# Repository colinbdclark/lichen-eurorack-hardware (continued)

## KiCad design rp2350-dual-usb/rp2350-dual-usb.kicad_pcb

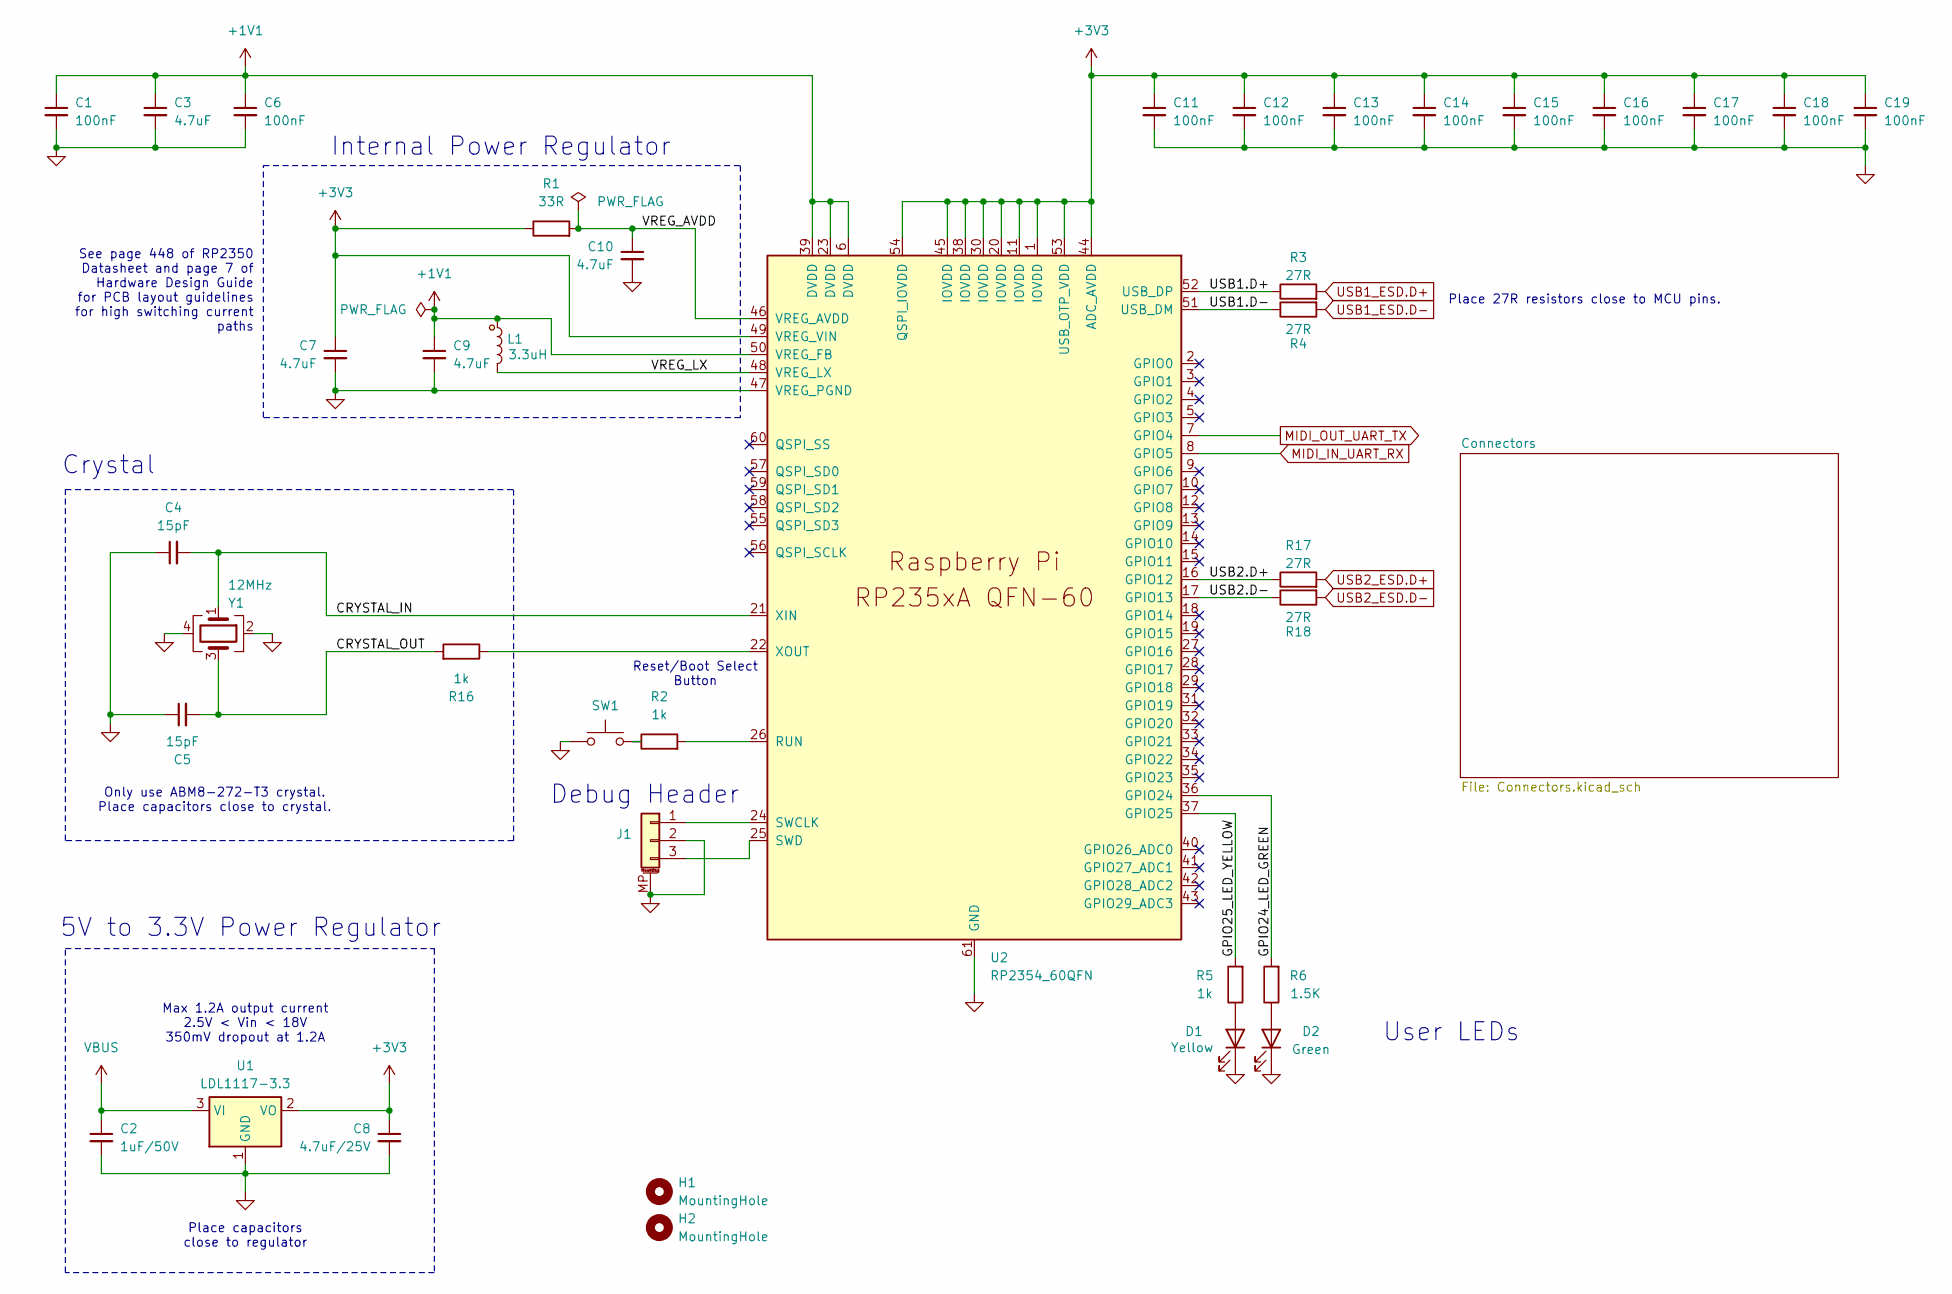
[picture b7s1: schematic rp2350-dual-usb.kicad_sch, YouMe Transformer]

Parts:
C1, C6, C11, C12, C13, C14, C15, C16, C17, C18, C19: 100nF; C_0402_1005Metric_small_pads; Part Number CL05B104KB54PNC; LCSC C307331
C2: 1uF; C_0805; Part Number CL21B105KBFNNNE; LCSC C28323
C3, C7, C9, C10: 4.7uF; C_0402_1005Metric_small_pads; Part Number CL05A475MP5NRNC; LCSC C23733
C4, C5: 15pF; C_0402_1005Metric_small_pads; Part Number 0402CG150J500NT; LCSC C1548
C8: 4.7uF; C_0805; Part Number CL21A475KAQNNNE; LCSC C1779
D1: Yellow; LED_0805_2012Metric_Pad1.15x1.40mm_HandSolder; Part Number KT-0805Y; LCSC C2296
D2: Green; LED_0805_2012Metric_Pad1.15x1.40mm_HandSolder; Part Number KT-0805G; LCSC C2297
H1, H2: MountingHole; MountingHole_2.2mm_M2
J1: Conn_01x03_MountingPin; JST_SH_SM03B-SRSS-TB_1x03-1MP_P1.00mm_Horizontal; Part Number SM03B-SRSS-TB; LCSC C160403
L1: 3.3uH; L_pol_2016; Part Number AOTA-B201610S3R3-101-T; LCSC C42411119
R1: 33R; R_0402_1005Metric; Part Number 0402WGF330JTCE; LCSC C25105
R2: 1k; R_0402_1005Metric; Part Number 0402WGF1001TCE; LCSC C11702
R3, R4, R17, R18: 27R; R_0402_1005Metric; Part Number 0402WGF270JTCE; LCSC C25100
R5, R16: 1K; R_0402_1005Metric; Part Number 0402WGF1001TCE; LCSC C11702
R6: 1.5K; R_0402_1005Metric; Part Number 0402WGF1501TCE; LCSC C25867
SW1: 1P1T Switch; SW_SPST_TS-1088-xR020; Part Number TS-1088-AR02016; LCSC C720477
U1: LDL1117-3.3; SOT-223-3_TabPin2; Part Number LDL1117S33R; LCSC C435835
U2: RP2354_60QFN; RP2350-QFN-60-1EP_7x7_P0.4mm_EP3.4x3.4mm_ThermalVias; Part Number RP2354A; LCSC C41378174
Y1: 12MHz; Crystal_SMD_3225-4Pin_3.2x2.5mm; Part Number ABM8-272-T3; LCSC C20625731

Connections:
+1V1: C1.1, C3.1, C6.1, C9.1, L1.1, U2.6 (DVDD), U2.23 (DVDD), U2.39 (DVDD), U2.50 (VREG_FB)
+3V3: C7.1, C8.1, C11.1, C12.1, C13.1, C14.1, C15.1, C16.1, C17.1, C18.1, C19.1, R1.1, U1.2 (VO), U2.1 (IOVDD), U2.11 (IOVDD), U2.20 (IOVDD), U2.30 (IOVDD), U2.38 (IOVDD), U2.44 (ADC_AVDD), U2.45 (IOVDD), U2.49 (VREG_VIN), U2.53 (USB_OTP_VDD), U2.54 (QSPI_IOVDD); also elsewhere on the board
/CRYSTAL_IN: C4.2, U2.21 (XIN), Y1.1
/CRYSTAL_OUT: C5.2, R16.2, Y1.3
/GPIO24_LED_GREEN: R6.2, U2.36 (GPIO24)
/GPIO25_LED_YELLOW: R5.2, U2.37 (GPIO25)
/USB1.D+: R3.1, U2.52 (USB_DP)
/USB1.D-: R4.1, U2.51 (USB_DM)
/USB2.D+: R17.1, U2.16 (GPIO12)
/USB2.D-: R18.1, U2.17 (GPIO13)
/VREG_AVDD: C10.1, R1.2, U2.46 (VREG_AVDD)
/VREG_LX: L1.2, U2.48 (VREG_LX)
GND: C1.2, C2.2, C3.2, C4.1, C5.1, C6.2, C7.2, C8.2, C9.2, C10.2, C11.2, C12.2, C13.2, C14.2, C15.2, C16.2, C17.2, C18.2, C19.2, D1.1 (K), D2.1 (K), J1.2, J1.MP (MountPin), SW1.1, U1.1 (GND), U2.47 (VREG_PGND), U2.61 (GND), Y1.2, Y1.4; also elsewhere on the board
MIDI_IN_UART_RX: U2.8 (GPIO5); also elsewhere on the board
MIDI_OUT_UART_TX: U2.7 (GPIO4); also elsewhere on the board
unnamed: D1.2 (A), R5.1
unnamed: D2.2 (A), R6.1
unnamed: J1.1, U2.24 (SWCLK)
unnamed: J1.3, U2.25 (SWD)
unnamed: R2.1, SW1.2
unnamed: R2.2, U2.26 (RUN)
unnamed: R16.1, U2.22 (XOUT)
USB1_ESD.D+: R3.2; also elsewhere on the board
USB1_ESD.D-: R4.2; also elsewhere on the board
USB2_ESD.D+: R17.2; also elsewhere on the board
USB2_ESD.D-: R18.2; also elsewhere on the board
VBUS: C2.1, U1.3 (VI); also elsewhere on the board

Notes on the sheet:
Place capacitors close to regulator
Place 27R resistors close to MCU pins.
5V to 3.3V Power Regulator
Max 1.2A output current 2.5V < Vin < 18V 350mV dropout at 1.2A
Debug Header
Reset/Boot Select Button
See page 448 of RP2350 Datasheet and page 7 of Hardware Design Guide for PCB layout guidelines for high switching current paths
User LEDs
Internal Power Regulator
Crystal
Only use ABM8-272-T3 crystal. Place capacitors close to crystal.

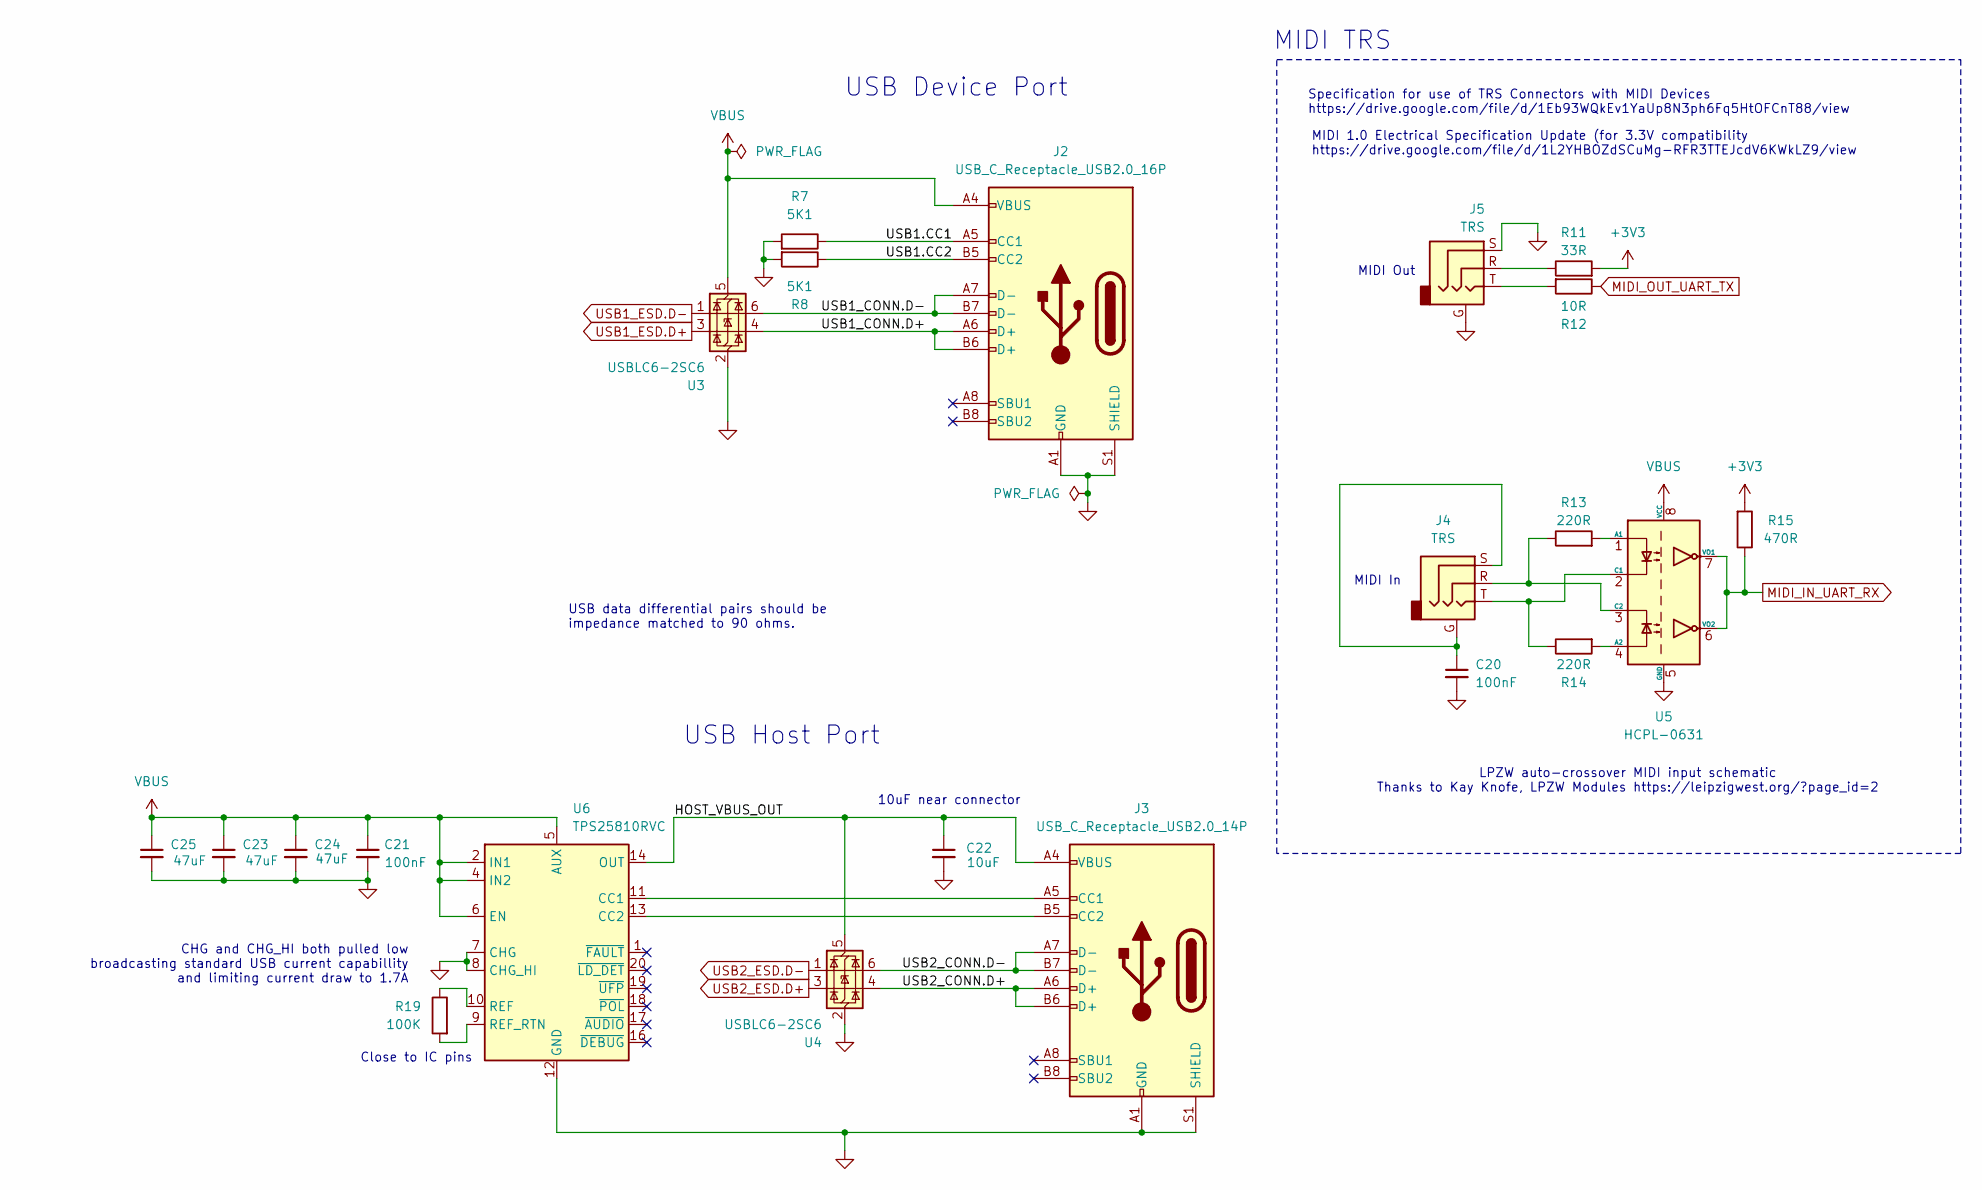
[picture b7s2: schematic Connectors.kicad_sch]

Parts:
C20: 100nF; C_0402_1005Metric_small_pads; Part Number CL05B104KB54PNC; LCSC C307331
C21: 100nF; C_0603; Part Number CC0603KRX7R9BB104; LCSC C14663
C22: 10uF; C_0603; Part Number CL10A106MA8NRNC; LCSC C96446
C23, C24, C25: 47uF; C_1206_3216Metric; Part Number CL31A476MPHNNNE; LCSC C96123
J2: USB_C_Receptacle_USB2.0_16P; USB_C_Receptacle_HRO_TYPE-C-31-M-12_Overhanging; Part Number TYPE-C-31-M-12; LCSC C165948
J3: USB_C_Receptacle_USB2.0_14P; USB_C_Receptacle_HRO_TYPE-C-31-M-12_Overhanging; Part Number TYPE-C-31-M-12; LCSC C165948
J4, J5: TRS; Jack_3.5mm_KoreanHropartsElec_PJ-320D-4A_Horizontal_Overhan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; Part Number PJ-320D-4A; LCSC C95562
R7, R8: 5.1K; R_0603; Part Number 0603WAF5101T5E; LCSC C23186
R11: 33R; R_0402_1005Metric; Part Number 0402WGF330JTCE; LCSC C25105
R12: 10R; R_0402_1005Metric; Part Number 0402WGF100JTCE; LCSC C25077
R13, R14: 220R; R_0402_1005Metric; Part Number 0402WGF2200TCE; LCSC C25091
R15: 470R; R_0402_1005Metric; Part Number 0402WGF4700TCE; LCSC C25117
R19: 100K; R_0402_1005Metric; Part Number 0402WGF1003TCE; LCSC C25741
U3, U4: USBLC6-2SC6; SOT-23-6; Part Number USBLC6-2SC6; LCSC C7519
U5: HCPL-0631; SOIC-8_3.9x4.9mm_P1.27mm; Part Number HCPL-0631-500E; LCSC C43949
U6: TPS25810RVC; Texas_RVC0020A_WQFN-20-1EP_3x4mm_P0.5mm_EP1.6x2.6mm_Thermal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; Part Number TPS25810RVCR; LCSC C473913

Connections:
+3V3: R11.2, R15.2; also elsewhere on the board
/Connectors/HOST_VBUS_OUT: C22.1, J3.A4 (VBUS), J3.A9 (VBUS), J3.B4 (VBUS), J3.B9 (VBUS), U4.5 (VBUS), U6.14 (OUT), U6.15 (OUT)
/Connectors/USB1.CC1: J2.A5 (CC1), R7.1
/Connectors/USB1.CC2: J2.B5 (CC2), R8.1
/Connectors/USB1_CONN.D+: J2.A6 (D+), J2.B6 (D+), U3.4 (I/O2)
/Connectors/USB1_CONN.D-: J2.A7 (D-), J2.B7 (D-), U3.6 (I/O1)
/Connectors/USB2_CONN.D+: J3.A6 (D+), J3.B6 (D+), U4.4 (I/O2)
/Connectors/USB2_CONN.D-: J3.A7 (D-), J3.B7 (D-), U4.6 (I/O1)
GND: C20.2, C21.2, C22.2, C23.2, C24.2, C25.2, J2.A1 (GND), J2.A12 (GND), J2.B1 (GND), J2.B12 (GND), J2.S1 (SHIELD), J3.A1 (GND), J3.A12 (GND), J3.B1 (GND), J3.B12 (GND), J3.S1 (SHIELD), J5.G, J5.S, R7.2, R8.2, U3.2 (GND), U4.2 (GND), U5.5 (GND), U6.7 (CHG), U6.8 (CHG_HI), U6.12 (GND), U6.21 (GND); also elsewhere on the board
MIDI_IN_UART_RX: R15.1, U5.6 (VO2), U5.7 (VO1); also elsewhere on the board
MIDI_OUT_UART_TX: R12.1; also elsewhere on the board
unnamed: C20.1, J4.G, J4.S
unnamed: J3.A5 (CC1), U6.11 (CC1)
unnamed: J3.B5 (CC2), U6.13 (CC2)
unnamed: J5.R, R11.1
unnamed: J5.T, R12.2
unnamed: R13.2, U5.1 (A1)
unnamed: R14.2, U5.4 (A2)
unnamed: J4.T, R14.1, U5.2 (C1)
unnamed: J4.R, R13.1, U5.3 (C2)
unnamed: R19.1, U6.10 (REF)
unnamed: R19.2, U6.9 (REF_RTN)
USB1_ESD.D+: U3.3 (I/O2); also elsewhere on the board
USB1_ESD.D-: U3.1 (I/O1); also elsewhere on the board
USB2_ESD.D+: U4.3 (I/O2); also elsewhere on the board
USB2_ESD.D-: U4.1 (I/O1); also elsewhere on the board
VBUS: C21.1, C23.1, C24.1, C25.1, J2.A4 (VBUS), J2.A9 (VBUS), J2.B4 (VBUS), J2.B9 (VBUS), U3.5 (VBUS), U5.8 (VCC), U6.2 (IN1), U6.3 (IN1), U6.4 (IN2), U6.5 (AUX), U6.6 (EN); also elsewhere on the board

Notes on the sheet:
CHG and CHG_HI both pulled low broadcasting standard USB current capabillity and limiting current draw to 1.7A
MIDI Out
10uF near connector
MIDI In
USB data differential pairs should be impedance matched to 90 ohms.
MIDI 1.0 Electrical Specification Update (for 3.3V compatibility https://drive.google.com/file/d/1L2YHBOZdSCuMg-RFR3TTEJcdV6KWkLZ9/view
MIDI TRS
Close to IC pins
Specification for use of TRS Connectors with MIDI Devices https://drive.google.com/file/d/1Eb93WQkEv1YaUp8N3ph6Fq5HtOFCnT88/view
USB Host Port
LPZW auto-crossover MIDI input schematic Thanks to Kay Knofe, LPZW Modules https://leipzigwest.org/?page_id=2
USB Device Port

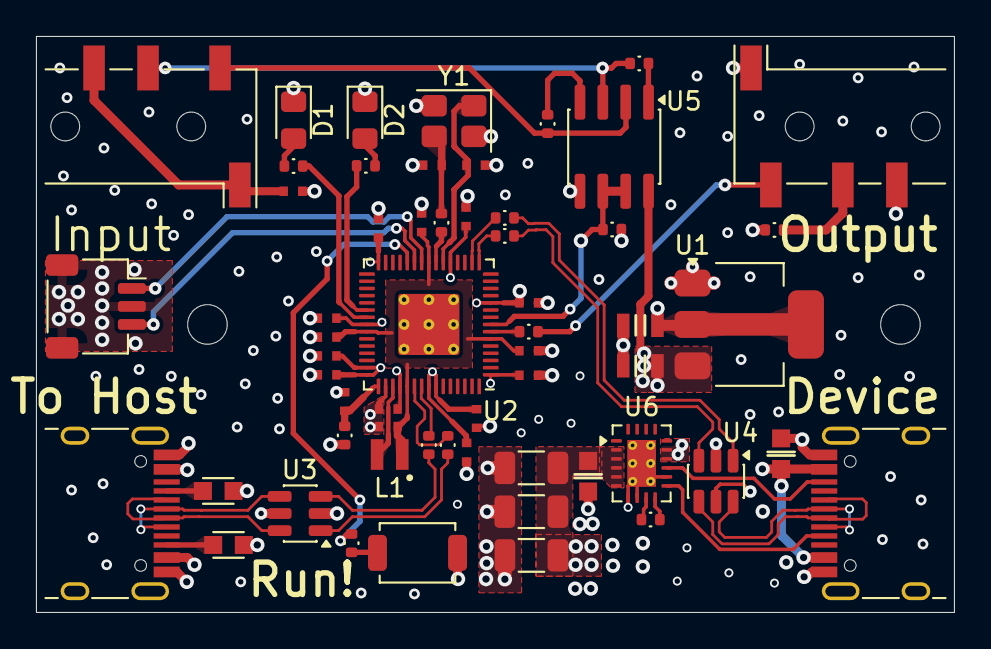
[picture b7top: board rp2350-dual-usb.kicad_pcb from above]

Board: 4 copper layers, 51.0 x 32.0 mm, 60 parts (0 on the bottom side), 45 nets.

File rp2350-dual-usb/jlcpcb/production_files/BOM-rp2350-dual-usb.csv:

Comment,Designator,Footprint,LCSC,Quantity
1K,"R16,R2,R5",R_0402_1005Metric,C11702,3
100nF,C21,C_0603,C14663,1
15pF,"C4,C5",C_0402_1005Metric_small_pads,C1548,2
Conn_01x03_MountingPin,J1,JST_SH_SM03B-SRSS-TB_1x03-1MP_P1.00mm_Horizontal,C160403,1
USB_C_Receptacle_USB2.0_16P,"J2,J3",USB_C_Receptacle_HRO_TYPE-C-31-M-12_Overhanging,C165948,2
4.7uF,C8,C_0805,C1779,1
12MHz,Y1,Crystal_SMD_3225-4Pin_3.2x2.5mm,C20625731,1
Yellow,D1,LED_0805_2012Metric_Pad1.15x1.40mm_HandSolder,C2296,1
Green,D2,LED_0805_2012Metric_Pad1.15x1.40mm_HandSolder,C2297,1
5.1K,"R7,R8",R_0603,C23186,2
4.7uF,"C10,C3,C7,C9",C_0402_1005Metric_small_pads,C23733,4
10R,R12,R_0402_1005Metric,C25077,1
220R,"R13,R14",R_0402_1005Metric,C25091,2
27R,"R17,R18,R3,R4",R_0402_1005Metric,C25100,4
33R,"R1,R11",R_0402_1005Metric,C25105,2
470R,R15,R_0402_1005Metric,C25117,1
100K,R19,R_0402_1005Metric,C25741,1
1.5K,R6,R_0402_1005Metric,C25867,1
1uF,C2,C_0805,C28323,1
100nF,"C1,C11,C12,C13,C14,C15,C16,C17,C18,C19,C20,C6",C_0402_1005Metric_small_pads,C307331,12
RP2354_60QFN,U2,RP2350-QFN-60-1EP_7x7_P0.4mm_EP3.4x3.4mm_ThermalVias,C41378174,1
3.3uH,L1,L_pol_2016,C42411119,1
LDL1117-3.3,U1,SOT-223-3_TabPin2,C435835,1
HCPL-0631,U5,SOIC-8_3.9x4.9mm_P1.27mm,C43949,1
TPS25810RVC,U6,Texas_RVC0020A_WQFN-20-1EP_3x4mm_P0.5mm_EP1.6x2.6mm_ThermalVias,C473913,1
1P1T Switch,SW1,SW_SPST_TS-1088-xR020,C720477,1
USBLC6-2SC6,"U3,U4",SOT-23-6,C7519,2
TRS,"J4,J5",Jack_3.5mm_KoreanHropartsElec_PJ-320D-4A_Horizontal_Overhanging,C95562,2
47uF,"C23,C24,C25",C_1206_3216Metric,C96123,3
10uF,C22,C_0603,C96446,1

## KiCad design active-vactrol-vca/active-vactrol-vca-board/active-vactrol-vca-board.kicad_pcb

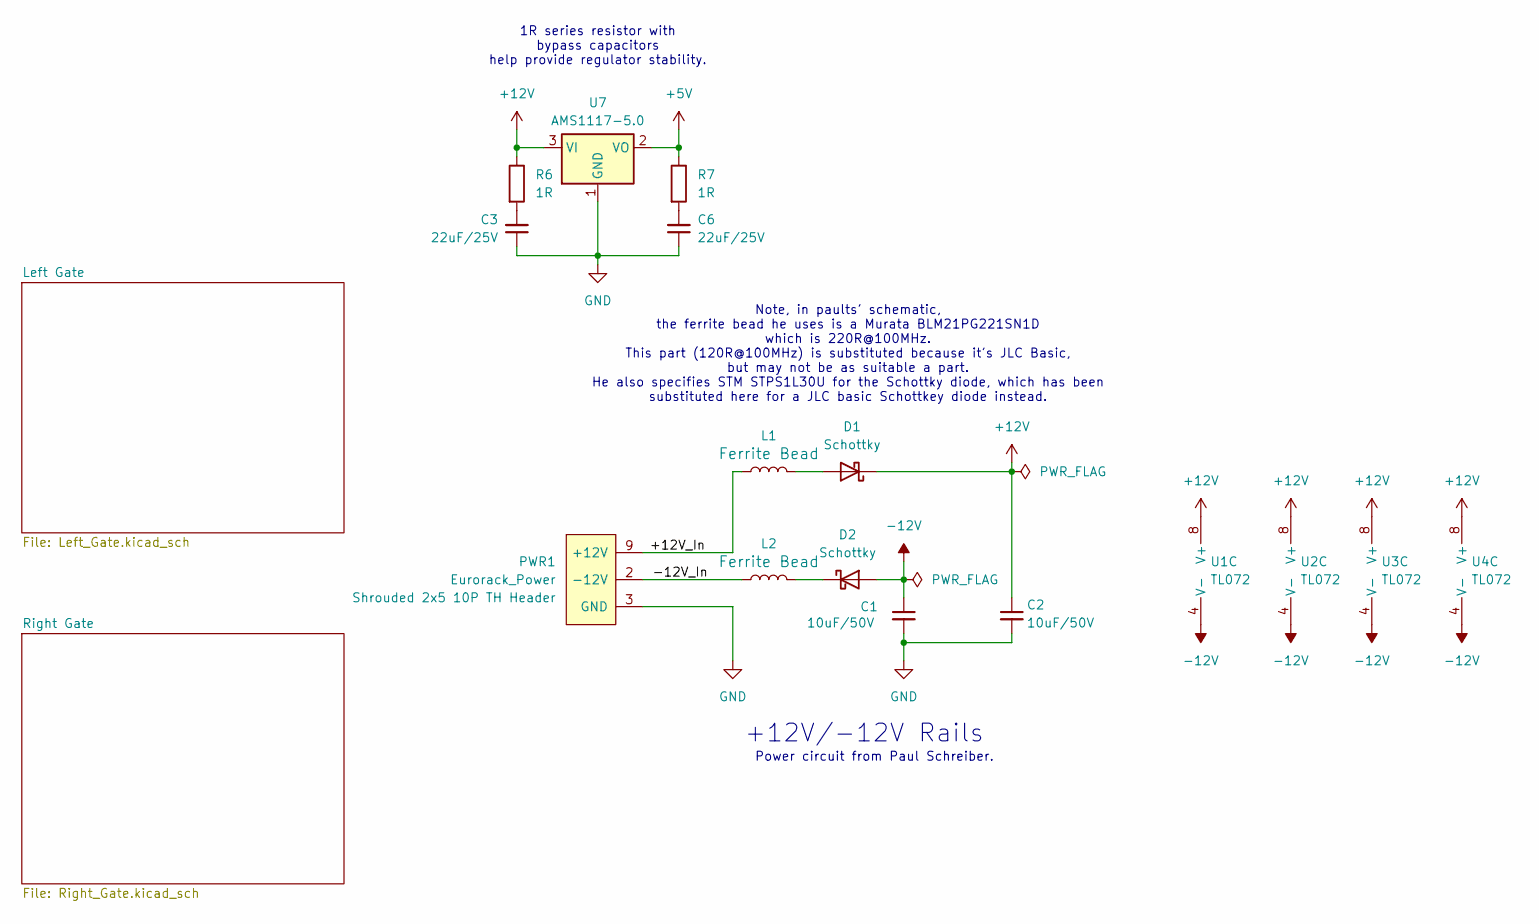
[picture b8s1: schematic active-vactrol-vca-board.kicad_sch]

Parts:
C1, C2: 10uF_0805_25V; C_0805; Part Number GRM21BR61H106KE43L; LCSC C440198
C3, C6: 22uF_0805_25V; C_0805; Part Number CL21A226MAQNNNE; LCSC C45783
D1, D2: Schottky; D_SMA_Handsoldering; Part Number SS34; LCSC C8678
L1, L2: FerriteBead_0603_2A; R_0603; Part Number BLM18PG121SN1D; LCSC C14709
PWR1: Eurorack_Power; Eurorack_Power_Shrouded_TH_Staggered_Small
R6, R7: 1R; R_0603; Part Number 0603WAF100KT5E; LCSC C22936
U1, U2, U3, U4: TL072; SOIC-8_3.9x4.9mm_P1.27mm; Part Number TL072CDT; LCSC C6961
U7: AMS1117-5.0; SOT-223-3_TabPin2; Part Number AMS1117-5.0; LCSC C6187

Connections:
+5V: R7.1, U7.2 (VO); also elsewhere on the board
+12V: C2.1, D1.1 (K), R6.1, U1.8 (V+), U2.8 (V+), U3.8 (V+), U4.8 (V+), U7.3 (VI)
-12V: C1.1, D2.2 (A), U1.4 (V-), U2.4 (V-), U3.4 (V-), U4.4 (V-)
/+12V_In: L1.1, PWR1.9 (+12V), PWR1.10 (+12V)
/-12V_In: L2.1, PWR1.1 (-12V), PWR1.2 (-12V)
GND: C1.2, C2.2, C3.1, C6.1, PWR1.3 (GND), PWR1.4 (GND), PWR1.5 (GND), PWR1.6 (GND), PWR1.7 (GND), PWR1.8 (GND), U7.1 (GND); also elsewhere on the board
unnamed: C3.2, R6.2
unnamed: C6.2, R7.2
unnamed: D1.2 (A), L1.2
unnamed: D2.1 (K), L2.2

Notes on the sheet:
1R series resistor with bypass capacitors help provide regulator stability.
Note, in paults' schematic, the ferrite bead he uses is a Murata BLM21PG221SN1D which is 220R@100MHz. This part (120R@100MHz) is substituted because it's JLC Basic, but may not be as suitable a part. He also specifies STM STPS1L30U for the Schottky diode, which has been substituted here for a JLC b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
Power circuit from Paul Schreiber.
+12V/-12V Rails

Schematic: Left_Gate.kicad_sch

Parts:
C4: 0.1uF film; C_Rect_L7.2mm_W2.5mm_P5.00mm_FKS2_FKP2_MKS2_MKP2
C5: 33pF C0G; C_0603; Part Number CL10C330JB8NNNC; LCSC C1663
J1, J2, J3: Thonkiconn_Mono_Audio_Jack; Audio_Jack_Thonkiconn_Mono_Left_Overhang; Part Number WQP518MA/PJ398SM
R1, R2, R3, R4, R5, R8, R20: 100k_0603; R_0603; Part Number 0603WAF1003T5E; LCSC C25803
R9: 1k_0603; R_0603; Part Number 0603WAF1001T5E; LCSC C21190
RV1: B10K; Potentiometer_Alpha_RD901_Eurorack; Part Number RD901F-40
U1, U2: TL072; SOIC-8_3.9x4.9mm_P1.27mm; Part Number TL072CDT; LCSC C6961
U5: NSL-32R3 60R@20mA; NSL-32

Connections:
+5V: R5.1; also elsewhere on the board
/Left Gate/L_BUFFERED: R4.2, U1.7, U5.3 (R)
/Left Gate/L_CV_ATTENUATED: RV1.2, U5.2 (K)
/Left Gate/L_CV_BUFFERED: R2.2, RV1.3, U1.1
/Left Gate/L_IN_UNBUFFERED: J2.T, R3.1
/Left Gate/L_VACTROL_OUTPUT: C4.1, U2.3 (+), U5.4 (R)
GND: C4.2, J1.S, J2.S, J3.S, RV1.1, U1.3 (+), U1.5 (+), U2.5 (+), U5.1 (A); also elsewhere on the board
L_CV_INPUT: J1.T, R1.1; also elsewhere on the board
L_OUTPUT: C5.1, J3.T, R8.2, R9.2; also elsewhere on the board
unnamed: J1.TN, R5.2
unnamed: R9.1, U2.7
unnamed: R1.2, R2.1, U1.2 (-)
unnamed: R3.2, R4.1, U1.6 (-)
unnamed: R20.1, U2.1, U2.2 (-)
unnamed: C5.2, R8.1, R20.2, U2.6 (-)

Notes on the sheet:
Unity gain buffer, 100k input impedance.
NSL-32SR3 resistance @ 20mA is 60R max cutoff frequency is: 0.1uF = 26.5KHz @ 20mA, 10.6KHz @ 5mA 0.15uF = 16.7KHz @ 20mA, 7.1KHz @ 5mA 0.22uF = 12.1Hz @ 20mA, 4.8KHz @ 5mA 0.47uF = 5.6KHz @ 20mA, 2.3KHz @ 5mA
Unity gain buffer, 1k output inpedance. Op amp feedback filter 48.2KHz cutoff
Vactrol LED connection is backwards, because the CV has been inverted.
CV attuenuator

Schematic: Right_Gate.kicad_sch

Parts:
C7: 0.1uF film; C_Rect_L7.2mm_W2.5mm_P5.00mm_FKS2_FKP2_MKS2_MKP2
C8: 33pF C0G; C_0603; Part Number CL10C330JB8NNNC; LCSC C1663
J4, J5, J6: Thonkiconn_Mono_Audio_Jack; Audio_Jack_Thonkiconn_Mono_Right_Overhang; Part Number WQP518MA/PJ398SM
R10, R11, R12, R13, R17, R19: 100k_0603; R_0603; Part Number 0603WAF1003T5E; LCSC C25803
R18: 1k_0603; R_0603; Part Number 0603WAF1001T5E; LCSC C21190
RV2: B10K; Potentiometer_Alpha_RD901_Eurorack; Part Number RD901F-40
U3, U4: TL072; SOIC-8_3.9x4.9mm_P1.27mm; Part Number TL072CDT; LCSC C6961
U6: NSL-32R3 60R@20mA; NSL-32

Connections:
/Right Gate/R_BUFFERED: R13.2, U3.7, U6.3 (R)
/Right Gate/R_CV_ATTENUATED: RV2.2, U6.2 (K)
/Right Gate/R_CV_BUFFERED: R11.2, RV2.3, U3.1
/Right Gate/R_CV_IN_UNBUFFERED: J4.T, R10.1
/Right Gate/R_IN_UNBUFFERED: J5.T, R12.1
/Right Gate/R_OUT_BUFFERED: C8.1, J6.T, R17.2, R18.2
/Right Gate/R_VACTROL_OUTPUT: C7.1, U4.3 (+), U6.4 (R)
GND: C7.2, J4.S, J5.S, J6.S, RV2.1, U3.3 (+), U3.5 (+), U4.5 (+), U6.1 (A); also elsewhere on the board
L_CV_INPUT: J4.TN; also elsewhere on the board
L_OUTPUT: J5.TN; also elsewhere on the board
unnamed: R18.1, U4.7
unnamed: R10.2, R11.1, U3.2 (-)
unnamed: R12.2, R13.1, U3.6 (-)
unnamed: R19.1, U4.1, U4.2 (-)
unnamed: C8.2, R17.1, R19.2, U4.6 (-)

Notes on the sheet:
CV attuenuator
Unity gain buffer, 100k input impedance.
NSL-32SR3 resistance @ 20mA is 60R max cutoff frequency is: 0.1uF = 26.5KHz @ 20mA, 10.6KHz @ 5mA 0.15uF = 16.7KHz @ 20mA, 7.1KHz @ 5mA 0.22uF = 12.1Hz @ 20mA, 4.8KHz @ 5mA 0.47uF = 5.6KHz @ 20mA, 2.3KHz @ 5mA
Unity gain buffer, 1k output inpedance. Op amp feedback filter 48.2KHz cutoff

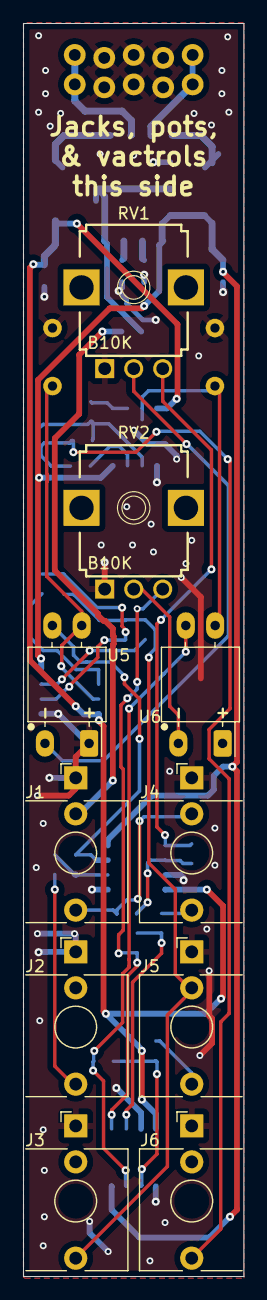
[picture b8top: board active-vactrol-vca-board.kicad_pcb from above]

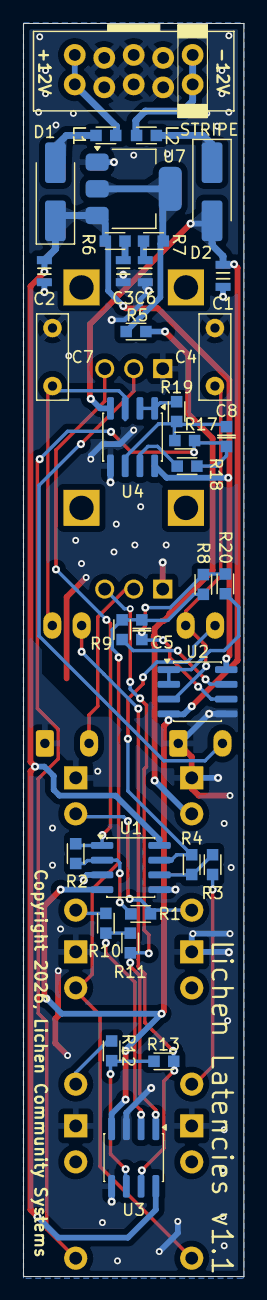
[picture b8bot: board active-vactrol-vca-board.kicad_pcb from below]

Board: 2 copper layers, 19.0 x 108.0 mm, 45 parts (35 on the bottom side), 35 nets.

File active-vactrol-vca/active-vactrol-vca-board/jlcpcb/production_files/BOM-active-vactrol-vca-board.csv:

Comment,Designator,Footprint,LCSC,Quantity
FerriteBead_0603_2A,"L1,L2",R_0603,C14709,2
33pF C0G,"C5,C8",C_0603,C1663,2
1k_0603,"R18,R9",R_0603,C21190,2
1R,"R6,R7",R_0603,C22936,2
100k_0603,"R1,R10,R11,R12,R13,R17,R19,R2,R20,R3,R4,R5,R8",R_0603,C25803,13
10uF_0805_25V,"C1,C2",C_0805,C440198,2
22uF_0805_25V,"C3,C6",C_0805,C45783,2
AMS1117-5.0,U7,SOT-223-3_TabPin2,C6187,1
TL072,"U1,U2,U3,U4",SOIC-8_3.9x4.9mm_P1.27mm,C6961,4
Schottky,"D1,D2",D_SMA_Handsoldering,C8678,2

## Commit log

2024-05-10 First commit of LCS's eurorack module hardware designs.
2024-05-10 Renames a couple of module directories.
2024-05-10 Updates Patch SM boards to non-exploding footprint.
2024-05-10 Fixes connections between jacks and switches on Lichen Sw. Now the panel is laid out so channels 1-3 are laid out sequentially.
2024-09-01 v1.1 of Freddie and Bifocals hardware.
2024-10-25 Updates Lichen component library and most module prototypes.
2024-10-31 Scales Lichen Four CV outputs to -8V to 8V to match audio outputs.
2025-09-14 Updates to Lichen symbols and footpints; adds RP2350 blocks.
2025-12-14 Updates KiCad symbols and footprints. Adds vactrol VCA.
2025-12-17 Adds v1.0 of Crustose and updates Vactrol VCA for production. Updates Lichen symbol and footprint library..
2025-12-17 Adds design blocks.
2025-12-30 Adds RP2350-based MIDI transformer, breadboard adaptors, and new design blocks.
2026-01-12 Updates Lichen symbols and footprints. Fixes to Crustose and Vactrol VCA. Adds 3D model of the RP2350 dual USB board.
2026-01-12 Adds STEP file for rp2350 dual USB board.
2026-01-18 Updates YouMe Transformer to v1.1, fixing incorrect R10 value. Improves the consistency of the Lichen symbol library.
2026-03-04 feat: Updates symbol libraries and design blocks. Adds in-progress RP2350-based module.
2026-03-05 feat: Adds NSL-33 dual vactrol symbol and footprint.
2026-03-17 Updates symbols, footprints, and design blocks.
2026-03-17 Updates YouMe Transformer to v1.2, adds USB host management IC.
2026-03-17 Adds in-progress stereo LPF based on Moritz Klein's design.
2026-04-07 feat: Updates Crustose, Cladonia and YouMe Transformer. Adds Stereo Latencies.
2026-04-20 fix: Uses correct VQFN-16 footprint. feat: Adds pin header version of Pico debugging port.
